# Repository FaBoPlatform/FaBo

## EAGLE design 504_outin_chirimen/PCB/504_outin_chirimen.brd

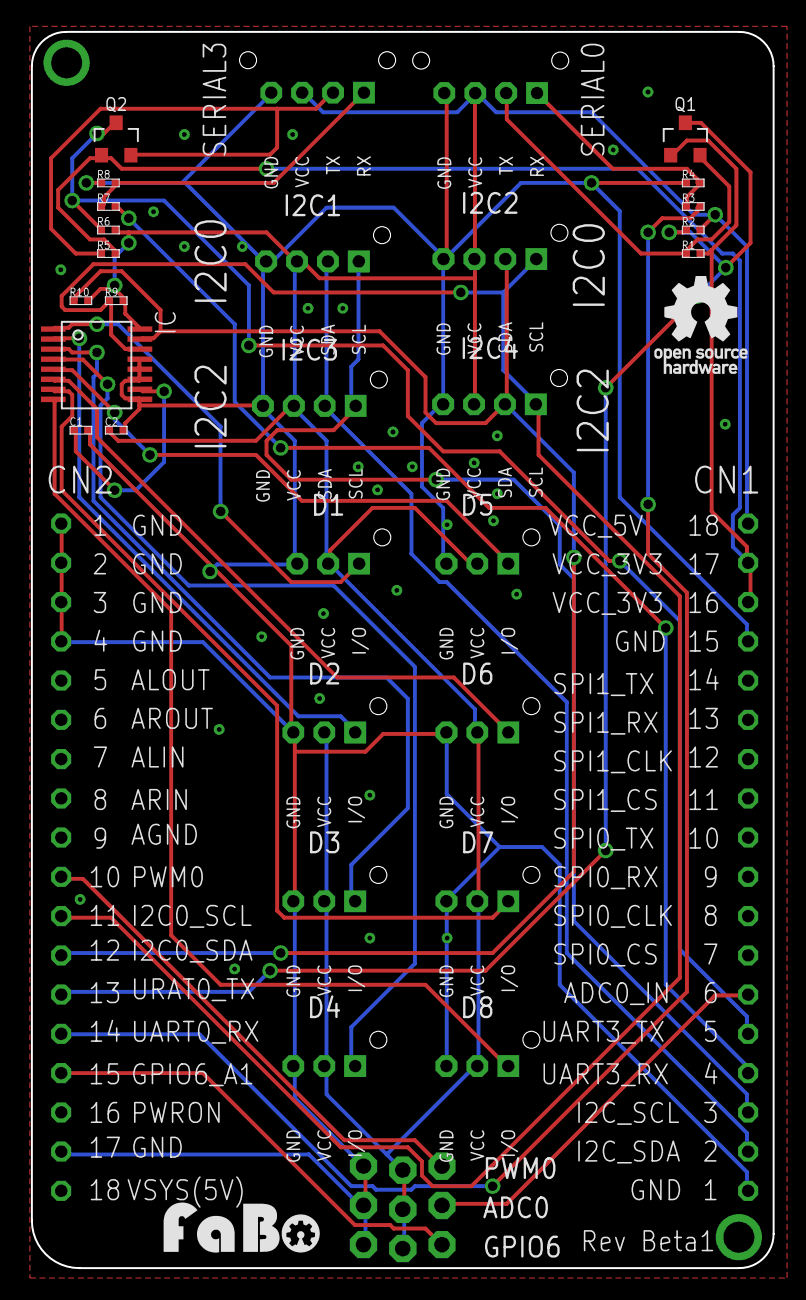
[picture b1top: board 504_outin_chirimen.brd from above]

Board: 2 copper layers, 48.0 x 80.0 mm, 35 parts (0 on the bottom side), 27 nets.

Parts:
ADC0: FABO_BRICK_3PIN_HEADER
C1: 0.1uf; 0402
C2: 1uf; 0402
D1, D2, D3, D4, D5, D6, D7, D8: FABO_BRICK_3PIN_B03B-PASK-1_SILK
GPIO6: FABO_BRICK_3PIN_HEADER
I2C1, I2C2, I2C3, I2C4: FABO_BRICK_I2C_B04B-PASK-1_SILK
IC: TI-ADS7828
J1, J2: FABO_BRICK_SERIAL_S04B-PASK-2_SILK
PWM0: FABO_BRICK_3PIN_HEADER
Q1, Q2: SOT23-3
R1, R2, R5, R6: 10k; 0402
R3, R7: 3k; 0402
R4, R8: 4.7k; 0402
R9, R10: 4.7K; 0402
U$2: FABO-CHIRIMEN
U$3: LOGO_OSHW_T_M
U$10: LOGO_FABO_MS

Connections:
3V3: Q1.1, Q2.1, R1.P$2, R5.P$2, U$2.CN1_16, U$2.CN1_17
5V: ADC0.VCC, C2.P$1, D1.VCC, D2.VCC, D3.VCC, D4.VCC, D5.VCC, D6.VCC, D7.VCC, D8.VCC, GPIO6.VCC, I2C1.VCC, I2C2.VCC, I2C3.VCC, I2C4.VCC, IC.16, J1.VCC, J2.VCC, PWM0.VCC, R2.P$2, R6.P$2, R9.P$2, R10.P$2, U$2.CN1_18
ADC0_IN: ADC0.I/O, U$2.CN1_6
CH0: D1.I/O, IC.1
CH1: D2.I/O, IC.2
CH2: D3.I/O, IC.3
CH3: D4.I/O, IC.4
CH4: D5.I/O, IC.5
CH5: D6.I/O, IC.6
CH6: D7.I/O, IC.7
CH7: D8.I/O, IC.8
GND: ADC0.GND, C1.P$2, C2.P$2, D1.GND, D2.GND, D3.GND, D4.GND, D5.GND, D6.GND, D7.GND, D8.GND, GPIO6.GND, I2C1.GND, I2C2.GND, I2C3.GND, I2C4.GND, IC.9, IC.11, IC.12, IC.13, J1.GND, J2.GND, PWM0.GND, R4.P$1, R8.P$1, U$2.CN1_1, U$2.CN1_15, U$2.CN2_1, U$2.CN2_2, U$2.CN2_3, U$2.CN2_4, U$2.CN2_17
GPIO6_A1: GPIO6.I/O, U$2.CN2_15
unnamed: C1.P$1, IC.10
PWM0: PWM0.I/O, U$2.CN2_10
RX0: J1.RX, R3.P$1, R4.P$2
RX3: J2.RX, R7.P$1, R8.P$2
SCL0: I2C2.SCL, I2C4.SCL, IC.14, R9.P$1, U$2.CN2_11
SCL2: I2C1.SCL, I2C3.SCL, U$2.CN1_3
SDA0: I2C2.SDA, I2C4.SDA, IC.15, R10.P$1, U$2.CN2_12
SDA2: I2C1.SDA, I2C3.SDA, U$2.CN1_2
TX0: J1.TX, Q1.2, R1.P$1
TX3: J2.TX, Q2.2, R5.P$1
UART0_RX: R3.P$2, U$2.CN2_14
UART0_TX: Q1.3, R2.P$1, U$2.CN2_13
UART3_RX: R7.P$2, U$2.CN1_4
UART3_TX: Q2.3, R6.P$1, U$2.CN1_5

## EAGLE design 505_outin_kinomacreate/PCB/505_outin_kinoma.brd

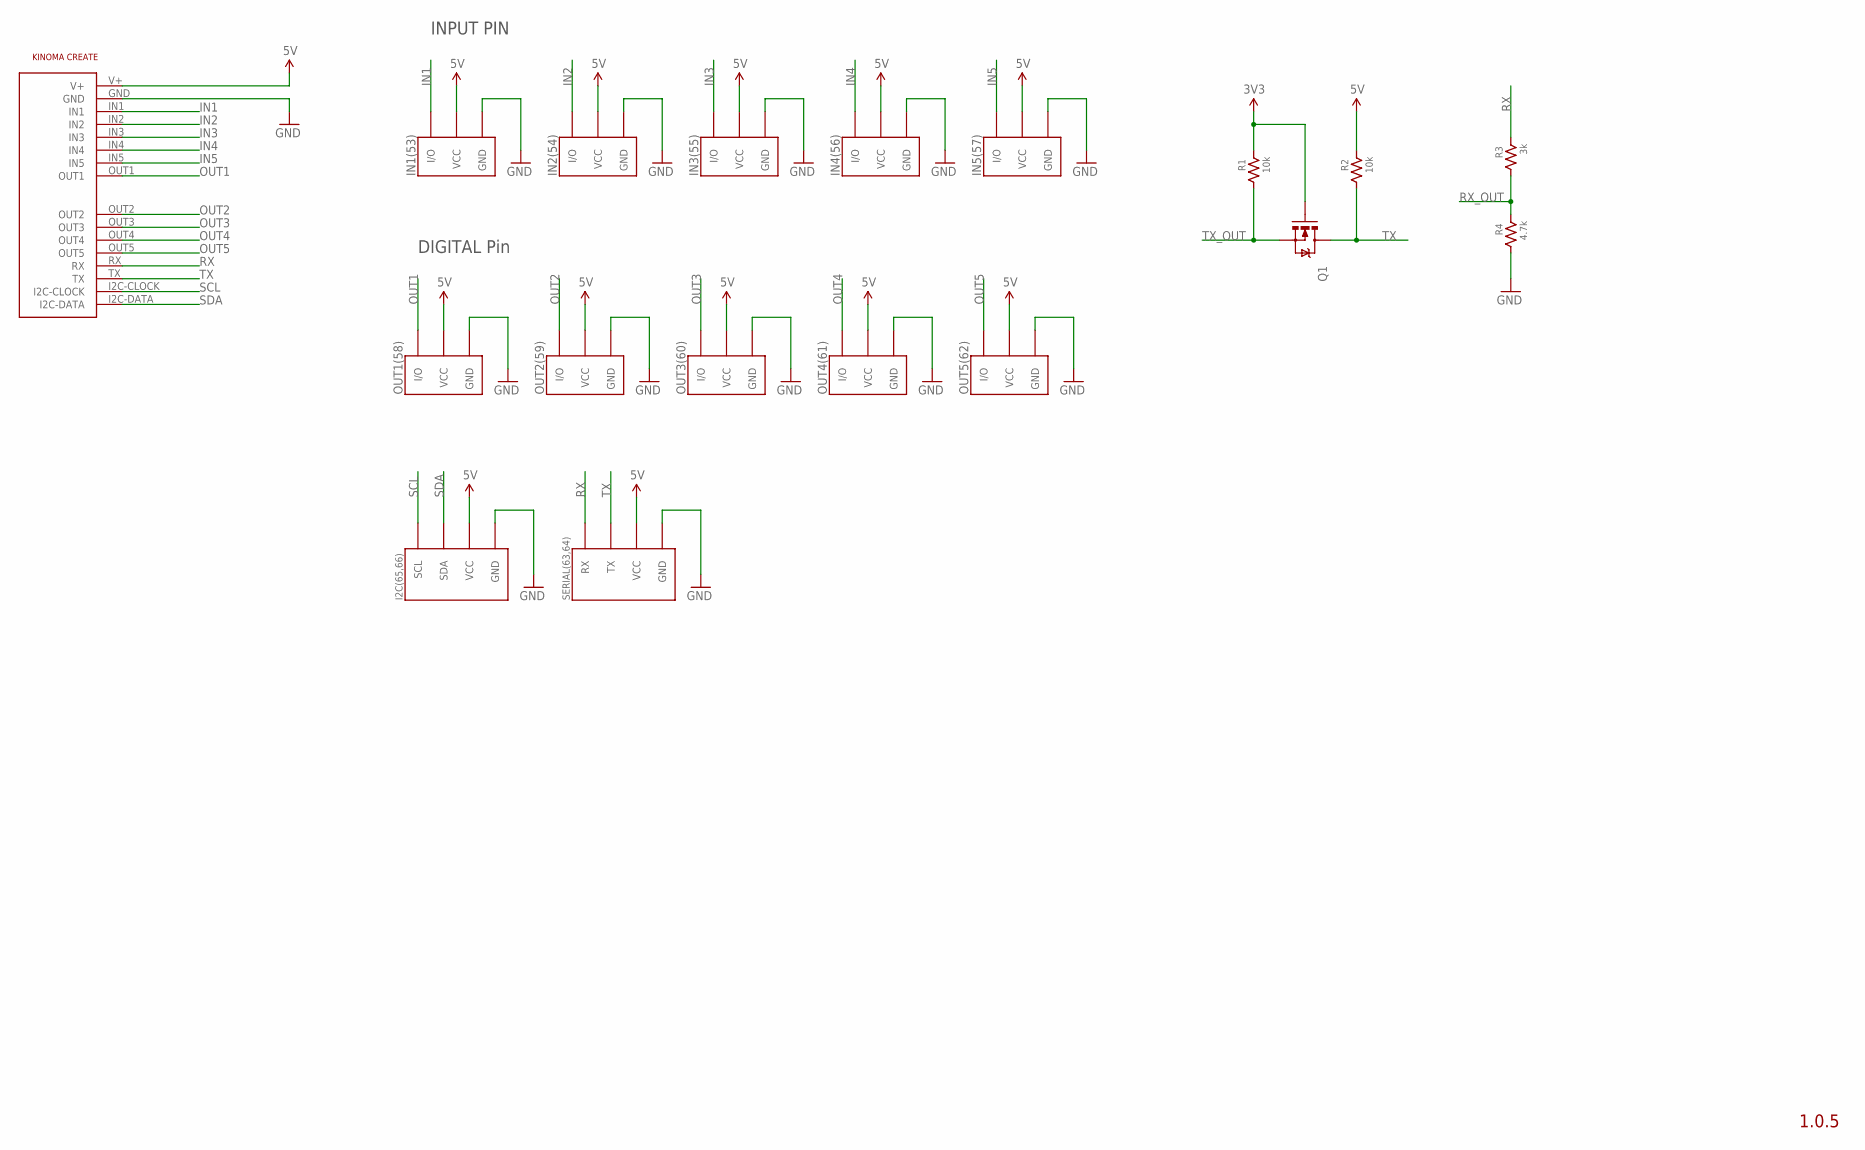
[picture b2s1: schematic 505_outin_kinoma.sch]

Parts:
I2C(65,66): I2C; FABO_BRICK_I2C_S04B-PASK-2
IN1(53), IN2(54), IN3(55), IN4(56), IN5(57): FABO_BRICK_3PIN-B03B-PASK-1; FABO_BRICK_3PIN_B03B-PASK-1
OUT1(58), OUT2(59), OUT3(60), OUT4(61), OUT5(62): FABO_BRICK_3PIN-B03B-PASK-1; FABO_BRICK_3PIN_B03B-PASK-1
Q1: MOSFET-N-BSS138; SOT23-3
R1, R2: 10k; 0402
R3: 3k; 0402
R4: 4.7k; 0402
SERIAL(63,64): FABO_BRICK_SERIAL-S04B-PASK-2; FABO_BRICK_SERIAL_S04B-PASK-2
U$18: FABO-KINOMA

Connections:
3V3: Q1.1 (G), R1.P$2 (2)
5V: I2C(65,66).VCC, IN1(53).VCC, IN2(54).VCC, IN3(55).VCC, IN4(56).VCC, IN5(57).VCC, OUT1(58).VCC, OUT2(59).VCC, OUT3(60).VCC, OUT4(61).VCC, OUT5(62).VCC, R2.P$2 (2), SERIAL(63,64).VCC, U$18.V+
GND: I2C(65,66).GND, IN1(53).GND, IN2(54).GND, IN3(55).GND, IN4(56).GND, IN5(57).GND, OUT1(58).GND, OUT2(59).GND, OUT3(60).GND, OUT4(61).GND, OUT5(62).GND, R4.P$1 (1), SERIAL(63,64).GND, U$18.GND
IN1: IN1(53).I/O, U$18.IN1
IN2: IN2(54).I/O, U$18.IN2
IN3: IN3(55).I/O, U$18.IN3
IN4: IN4(56).I/O, U$18.IN4
IN5: IN5(57).I/O, U$18.IN5
OUT1: OUT1(58).I/O, U$18.OUT1
OUT2: OUT2(59).I/O, U$18.OUT2
OUT3: OUT3(60).I/O, U$18.OUT3
OUT4: OUT4(61).I/O, U$18.OUT4
OUT5: OUT5(62).I/O, U$18.OUT5
RX: R3.P$2 (2), SERIAL(63,64).RX, U$18.RX
RX_OUT: R3.P$1 (1), R4.P$2 (2)
SCL: I2C(65,66).SCL, U$18.I2C-CLOCK
SDA: I2C(65,66).SDA, U$18.I2C-DATA
TX: Q1.3 (D), R2.P$1 (1), SERIAL(63,64).TX, U$18.TX
TX_OUT: Q1.2 (S), R1.P$1 (1)

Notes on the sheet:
1.0.5
DIGITAL Pin
INPUT PIN

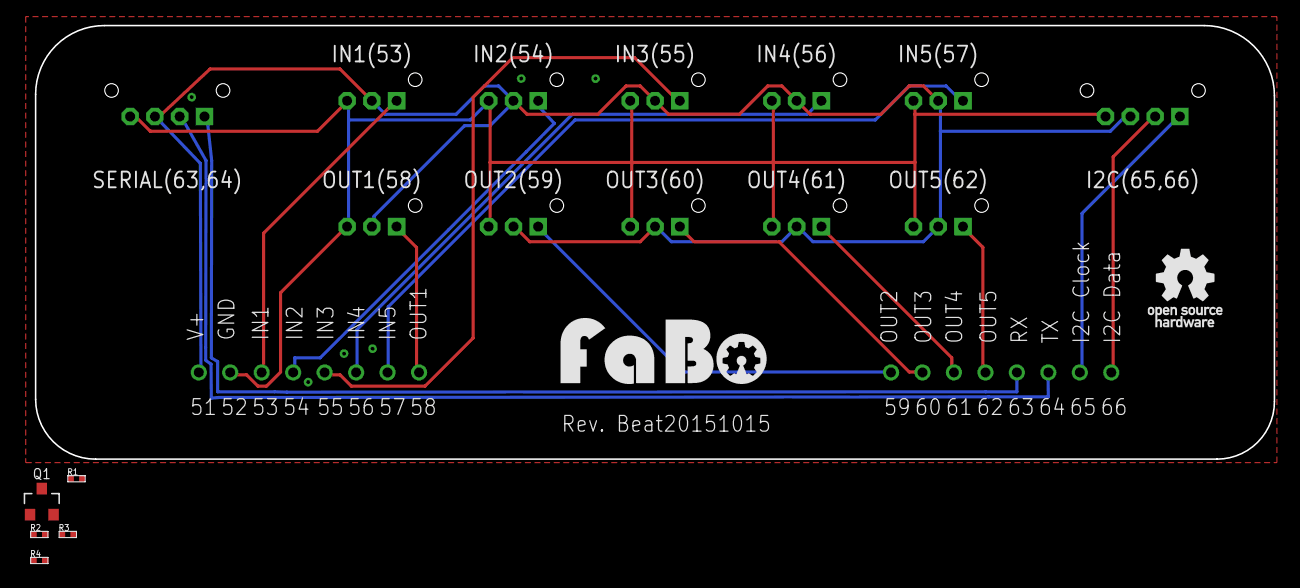
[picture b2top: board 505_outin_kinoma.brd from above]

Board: 2 copper layers, 100.0 x 35.0 mm, 20 parts (0 on the bottom side), 19 nets.

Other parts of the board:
U$2: LOGO_FABO_L
U$3: LOGO_OSHW_T_M

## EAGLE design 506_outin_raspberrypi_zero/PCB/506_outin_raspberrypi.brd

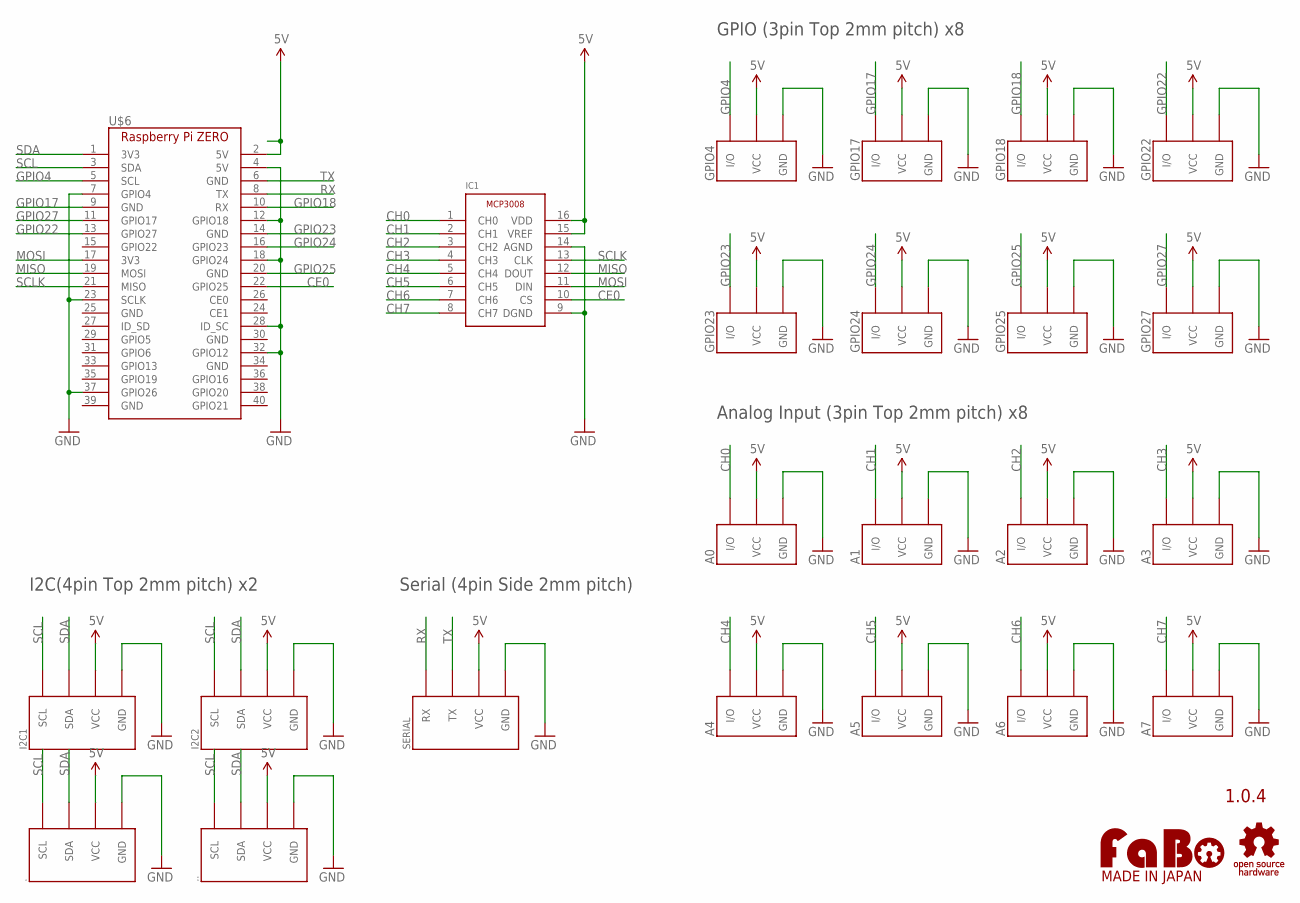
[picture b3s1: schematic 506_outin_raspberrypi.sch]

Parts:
., ..: FABO_BRICK_I2C-B04B-PASK-1; FABO_BRICK_I2C_B04B-PASK-1
A0, A1, A2, A3, A4, A5, A6, A7: FABO_BRICK_3PIN-B03B-PASK-1; FABO_BRICK_3PIN_B03B-PASK-1
GPIO4, GPIO17, GPIO18, GPIO22, GPIO23, GPIO24, GPIO25, GPIO27: FABO_BRICK_3PIN-B03B-PASK-1; FABO_BRICK_3PIN_B03B-PASK-1
I2C1, I2C2: FABO_BRICK_I2C-B04B-PASK-1; FABO_BRICK_I2C_B04B-PASK-1
IC1: MICROCHIP-MCP3008
SERIAL: FABO_BRICK_SERIAL-S04B-PASK-2; FABO_BRICK_SERIAL_S04B-PASK-2
U$4: LOGO_OSHW-T_M; LOGO_OSHW_T_MS
U$6: RASPBERRY_PI_ZERO
U$14: LOGO_FABO-M; LOGO_FABO_MS

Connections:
5V: ..VCC, ...VCC, A0.VCC, A1.VCC, A2.VCC, A3.VCC, A4.VCC, A5.VCC, A6.VCC, A7.VCC, GPIO4.VCC, GPIO17.VCC, GPIO18.VCC, GPIO22.VCC, GPIO23.VCC, GPIO24.VCC, GPIO25.VCC, GPIO27.VCC, I2C1.VCC, I2C2.VCC, IC1.15 (VREF), IC1.16 (VDD), SERIAL.VCC, U$6.2 (5V)
CE0: IC1.10 (CS), U$6.22 (GPIO25)
CH0: A0.I/O, IC1.1 (CH0)
CH1: A1.I/O, IC1.2 (CH1)
CH2: A2.I/O, IC1.3 (CH2)
CH3: A3.I/O, IC1.4 (CH3)
CH4: A4.I/O, IC1.5 (CH4)
CH5: A5.I/O, IC1.6 (CH5)
CH6: A6.I/O, IC1.7 (CH6)
CH7: A7.I/O, IC1.8 (CH7)
GND: ..GND, ...GND, A0.GND, A1.GND, A2.GND, A3.GND, A4.GND, A5.GND, A6.GND, A7.GND, GPIO4.GND, GPIO17.GND, GPIO18.GND, GPIO22.GND, GPIO23.GND, GPIO24.GND, GPIO25.GND, GPIO27.GND, I2C1.GND, I2C2.GND, IC1.9 (DGND), IC1.14 (AGND), SERIAL.GND, U$6.4 (5V), U$6.7 (GPIO4), U$6.12 (GPIO18), U$6.18 (GPIO24), U$6.23 (SCLK), U$6.28 (ID_SC), U$6.32 (GPIO12), U$6.37 (GPIO26)
GPIO4: GPIO4.I/O, U$6.5 (SCL)
GPIO17: GPIO17.I/O, U$6.9 (GND)
GPIO18: GPIO18.I/O, U$6.10 (RX)
GPIO22: GPIO22.I/O, U$6.13 (GPIO27)
GPIO23: GPIO23.I/O, U$6.14 (GND)
GPIO24: GPIO24.I/O, U$6.16 (GPIO23)
GPIO25: GPIO25.I/O, U$6.20 (GND)
GPIO27: GPIO27.I/O, U$6.11 (GPIO17)
MISO: IC1.12 (DOUT), U$6.19 (MOSI)
MOSI: IC1.11 (DIN), U$6.17 (3V3)
RX: SERIAL.RX, U$6.8 (TX)
SCL: ..SCL, ...SCL, I2C1.SCL, I2C2.SCL, U$6.3 (SDA)
SCLK: IC1.13 (CLK), U$6.21 (MISO)
SDA: ..SDA, ...SDA, I2C1.SDA, I2C2.SDA, U$6.1 (3V3)
TX: SERIAL.TX, U$6.6 (GND)

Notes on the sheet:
1.0.4
GPIO (3pin Top 2mm pitch) x8
I2C(4pin Top 2mm pitch) x2
Analog Input (3pin Top 2mm pitch) x8
Serial (4pin Side 2mm pitch)

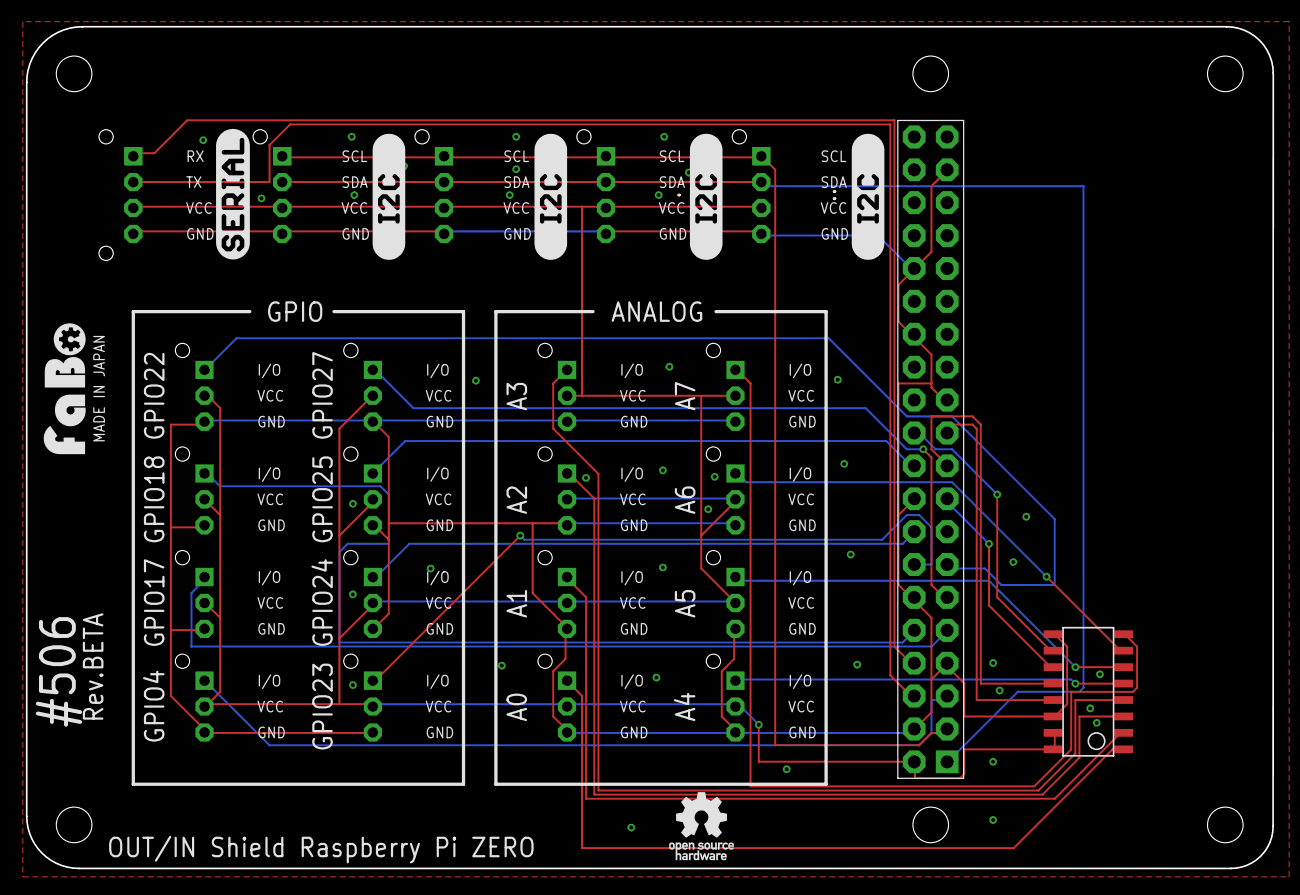
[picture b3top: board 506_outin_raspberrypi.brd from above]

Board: 2 copper layers, 96.3 x 65.0 mm, 30 parts (0 on the bottom side), 26 nets.

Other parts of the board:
U$2, U$5, U$7, U$8: LOGO_SILK_I2C
U$3: LOGO_SILK_SERIAL2

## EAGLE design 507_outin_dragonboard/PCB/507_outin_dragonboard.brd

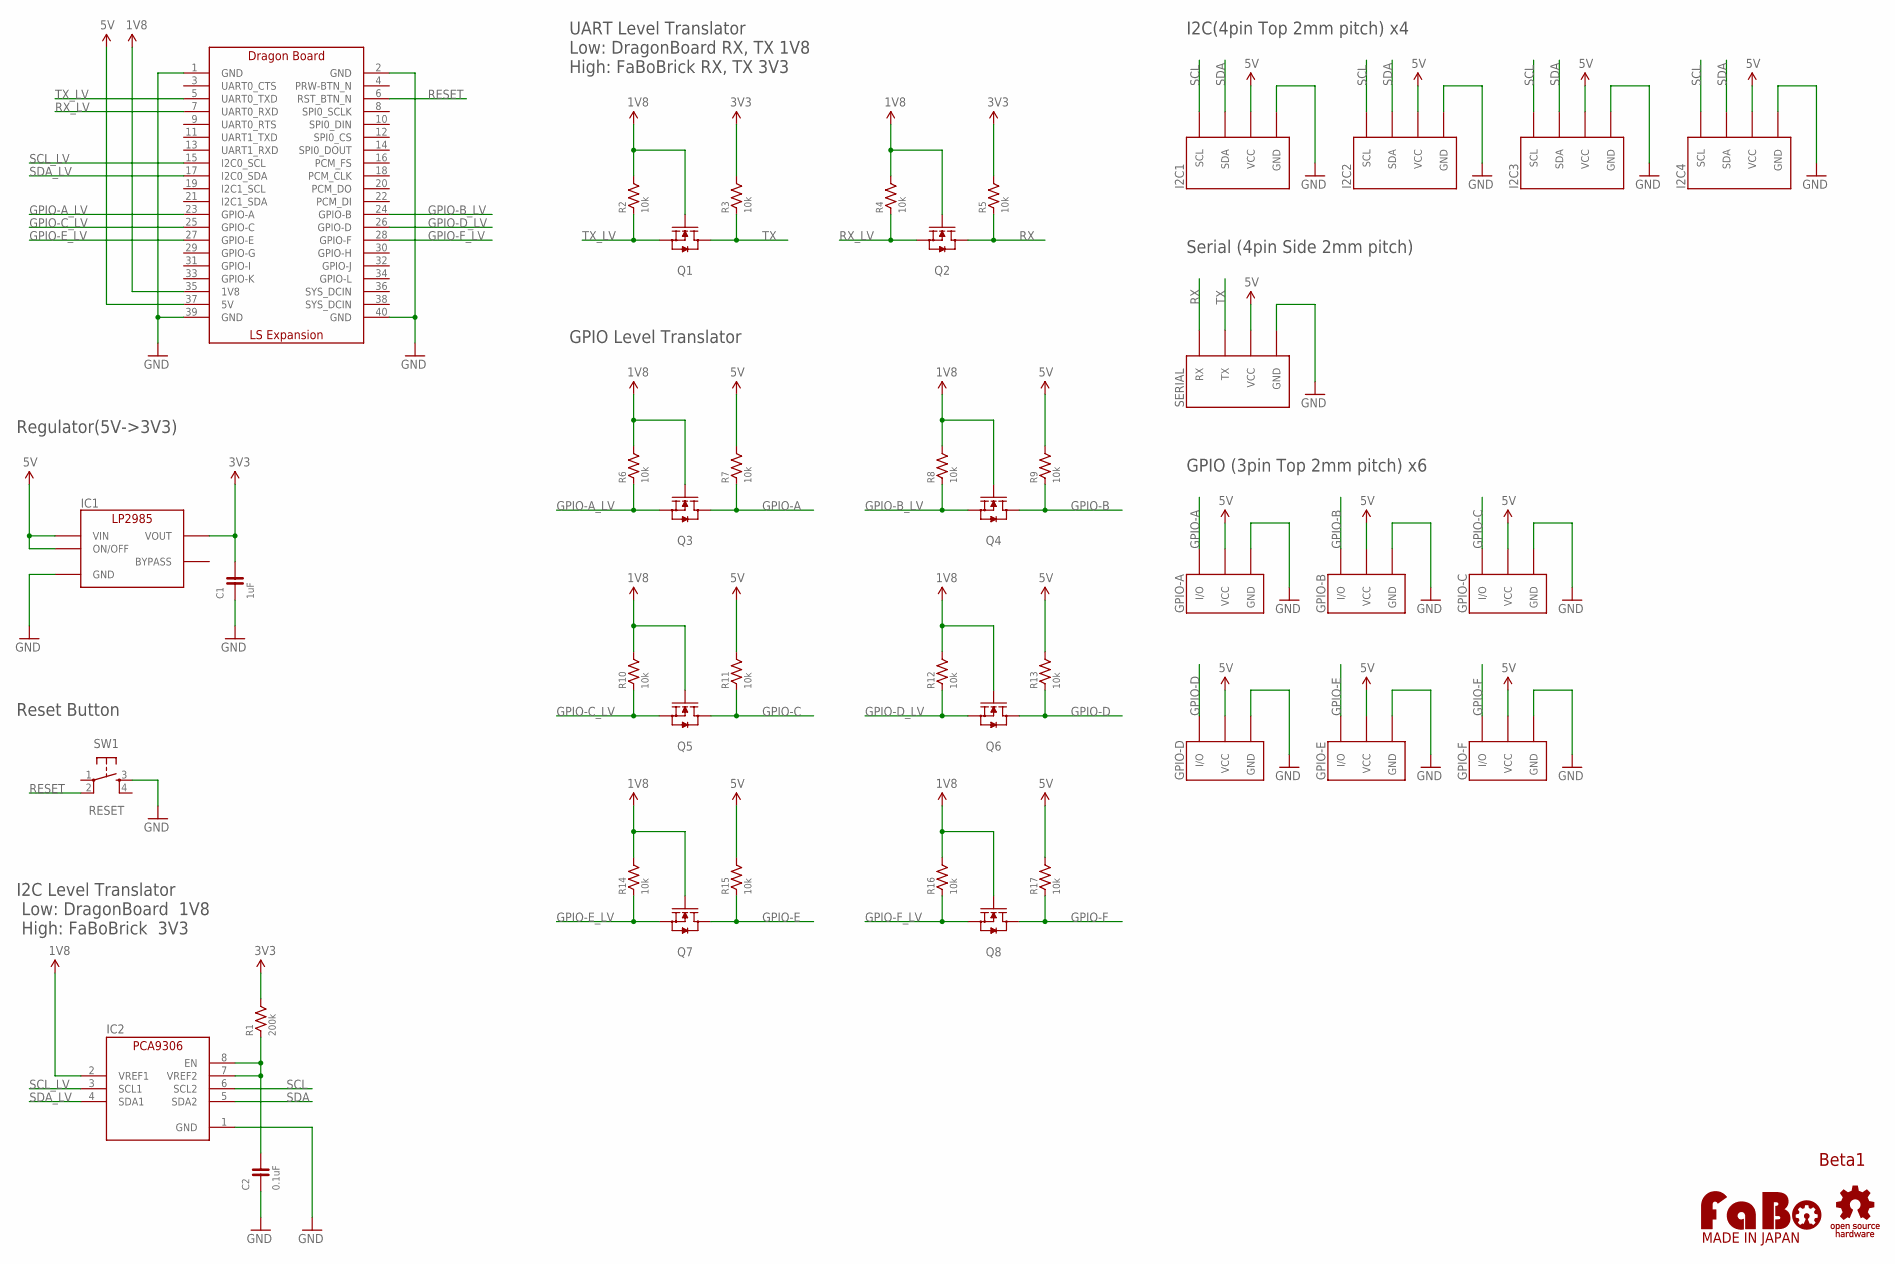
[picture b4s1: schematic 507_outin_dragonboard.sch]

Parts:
C1: 1uF; 0603
C2: 0.1uF; 0603
GPIO-A: FABO_BRICK_3PIN-B03B-PASK-1; FABO_BRICK_3PIN_B03B-PASK-1
GPIO-B: FABO_BRICK_3PIN-B03B-PASK-1; FABO_BRICK_3PIN_B03B-PASK-1
GPIO-C: FABO_BRICK_3PIN-B03B-PASK-1; FABO_BRICK_3PIN_B03B-PASK-1
GPIO-D: FABO_BRICK_3PIN-B03B-PASK-1; FABO_BRICK_3PIN_B03B-PASK-1
GPIO-E: FABO_BRICK_3PIN-B03B-PASK-1; FABO_BRICK_3PIN_B03B-PASK-1
GPIO-F: FABO_BRICK_3PIN-B03B-PASK-1; FABO_BRICK_3PIN_B03B-PASK-1
I2C1, I2C2, I2C3, I2C4: FABO_BRICK_I2C-B04B-PASK-1; FABO_BRICK_I2C_B04B-PASK-1
IC1: TI-LP2985-33DBVR; TI-LP2985
IC2: TI-PCA9306DQE; TI-PCA9306
Q1, Q2, Q3, Q4, Q5, Q6, Q7, Q8: MOSFET-N-BSS138; SOT23-3
R1: 200k; 0603
R2, R3, R4, R5, R6, R7, R8, R9, R10, R11, R12, R13, R14, R15, R16, R17: 10k; 0603
SERIAL: FABO_BRICK_SERIAL-S04B-PASK-2; FABO_BRICK_SERIAL_S04B-PASK-2
SW1: RESET; DTS_6_V
U1: FABO-DRAGONBOARD
U$4: LOGO_OSHW-T_M_BOTTOM; LOGO_OSHW_T_MS_BOTTOM
U$8: LOGO_FABO-M; LOGO_FABO_MS

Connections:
1V8: IC2.2 (VREF1), Q1.1 (G), Q2.1 (G), Q3.1 (G), Q4.1 (G), Q5.1 (G), Q6.1 (G), Q7.1 (G), Q8.1 (G), R2.2, R4.2, R6.2, R8.2, R10.2, R12.2, R14.2, R16.2, U1.35 (1V8)
3V3: C1.2, IC1.5 (VOUT), R1.2, R3.2, R5.2
5V: GPIO-A.VCC, GPIO-B.VCC, GPIO-C.VCC, GPIO-D.VCC, GPIO-E.VCC, GPIO-F.VCC, I2C1.VCC, I2C2.VCC, I2C3.VCC, I2C4.VCC, IC1.1 (VIN), IC1.3 (ON/OFF), R7.2, R9.2, R11.2, R13.2, R15.2, R17.2, SERIAL.VCC, U1.37 (5V)
GND: C1.1, C2.1, GPIO-A.GND, GPIO-B.GND, GPIO-C.GND, GPIO-D.GND, GPIO-E.GND, GPIO-F.GND, I2C1.GND, I2C2.GND, I2C3.GND, I2C4.GND, IC1.2 (GND), IC2.1 (GND), SERIAL.GND, SW1.3, U1.1 (GND), U1.2 (GND), U1.39 (GND), U1.40 (GND)
GPIO-A: GPIO-A.I/O, Q3.3 (D), R7.1
GPIO-A_LV: Q3.2 (S), R6.1, U1.23 (GPIO-A)
GPIO-B: GPIO-B.I/O, Q4.3 (D), R9.1
GPIO-B_LV: Q4.2 (S), R8.1, U1.24 (GPIO-B)
GPIO-C: GPIO-C.I/O, Q5.3 (D), R11.1
GPIO-C_LV: Q5.2 (S), R10.1, U1.25 (GPIO-C)
GPIO-D: GPIO-D.I/O, Q6.3 (D), R13.1
GPIO-D_LV: Q6.2 (S), R12.1, U1.26 (GPIO-D)
GPIO-E: GPIO-E.I/O, Q7.3 (D), R15.1
GPIO-E_LV: Q7.2 (S), R14.1, U1.27 (GPIO-E)
GPIO-F: GPIO-F.I/O, Q8.3 (D), R17.1
GPIO-F_LV: Q8.2 (S), R16.1, U1.28 (GPIO-F)
unnamed: C2.2, IC2.7 (VREF2), IC2.8 (EN), R1.1
RESET: SW1.2, U1.6 (RST_BTN_N)
RX: Q2.3 (D), R5.1, SERIAL.RX
RX_LV: Q2.2 (S), R4.1, U1.7 (UART0_RXD)
SCL: I2C1.SCL, I2C2.SCL, I2C3.SCL, I2C4.SCL, IC2.6 (SCL2)
SCL_LV: IC2.3 (SCL1), U1.15 (I2C0_SCL)
SDA: I2C1.SDA, I2C2.SDA, I2C3.SDA, I2C4.SDA, IC2.5 (SDA2)
SDA_LV: IC2.4 (SDA1), U1.17 (I2C0_SDA)
TX: Q1.3 (D), R3.1, SERIAL.TX
TX_LV: Q1.2 (S), R2.1, U1.5 (UART0_TXD)

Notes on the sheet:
Beta1
UART Level Translator Low: DragonBoard RX, TX 1V8 High: FaBoBrick RX, TX 3V3
I2C(4pin Top 2mm pitch) x4
Serial (4pin Side 2mm pitch)
I2C Level Translator Low: DragonBoard 1V8 High: FaBoBrick 3V3
Regulator(5V->3V3)
Reset Button
GPIO (3pin Top 2mm pitch) x6
GPIO Level Translator

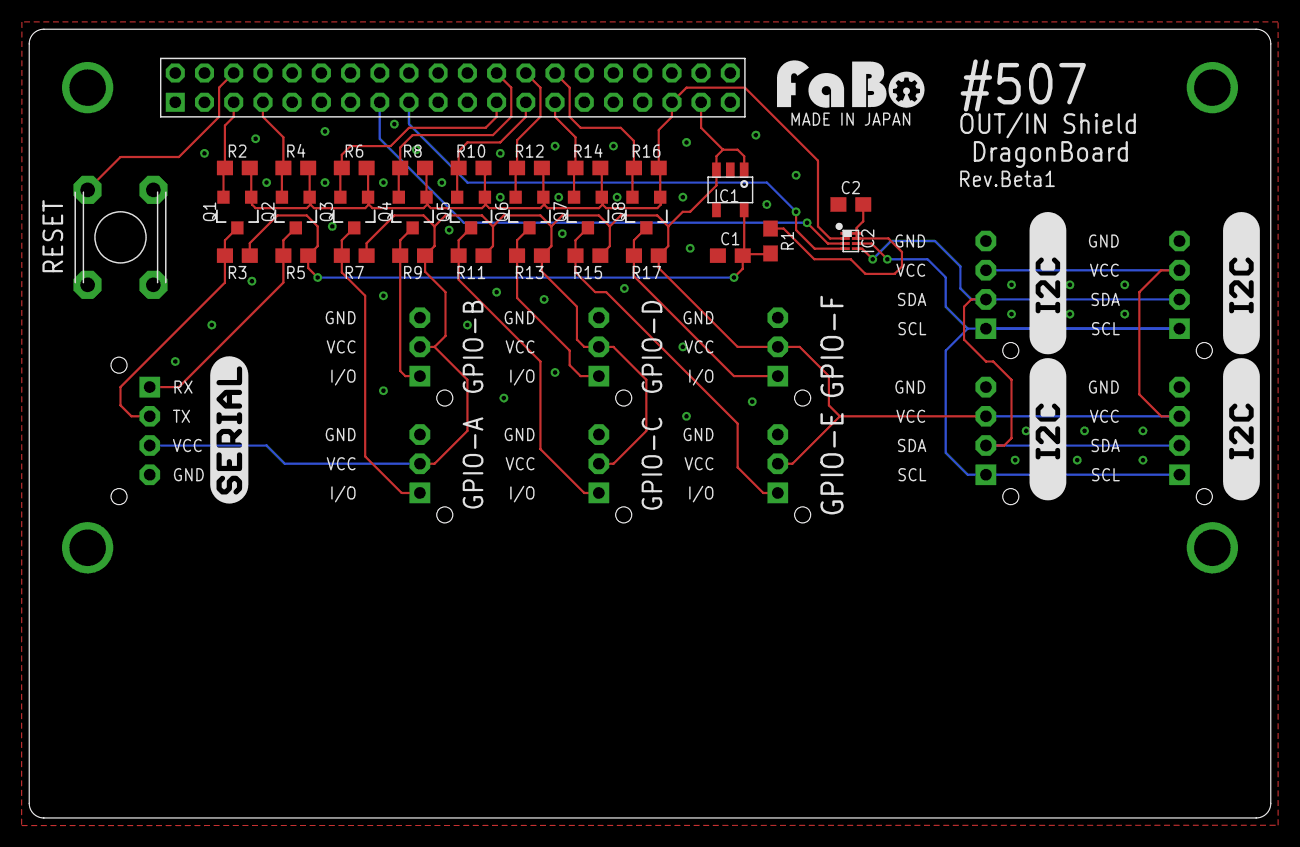
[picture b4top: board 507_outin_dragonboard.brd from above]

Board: 2 copper layers, 85.0 x 54.0 mm, 49 parts (0 on the bottom side), 26 nets.

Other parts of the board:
U$2, U$5, U$6, U$7: LOGO_SILK_I2C
U$3: LOGO_SILK_SERIAL2

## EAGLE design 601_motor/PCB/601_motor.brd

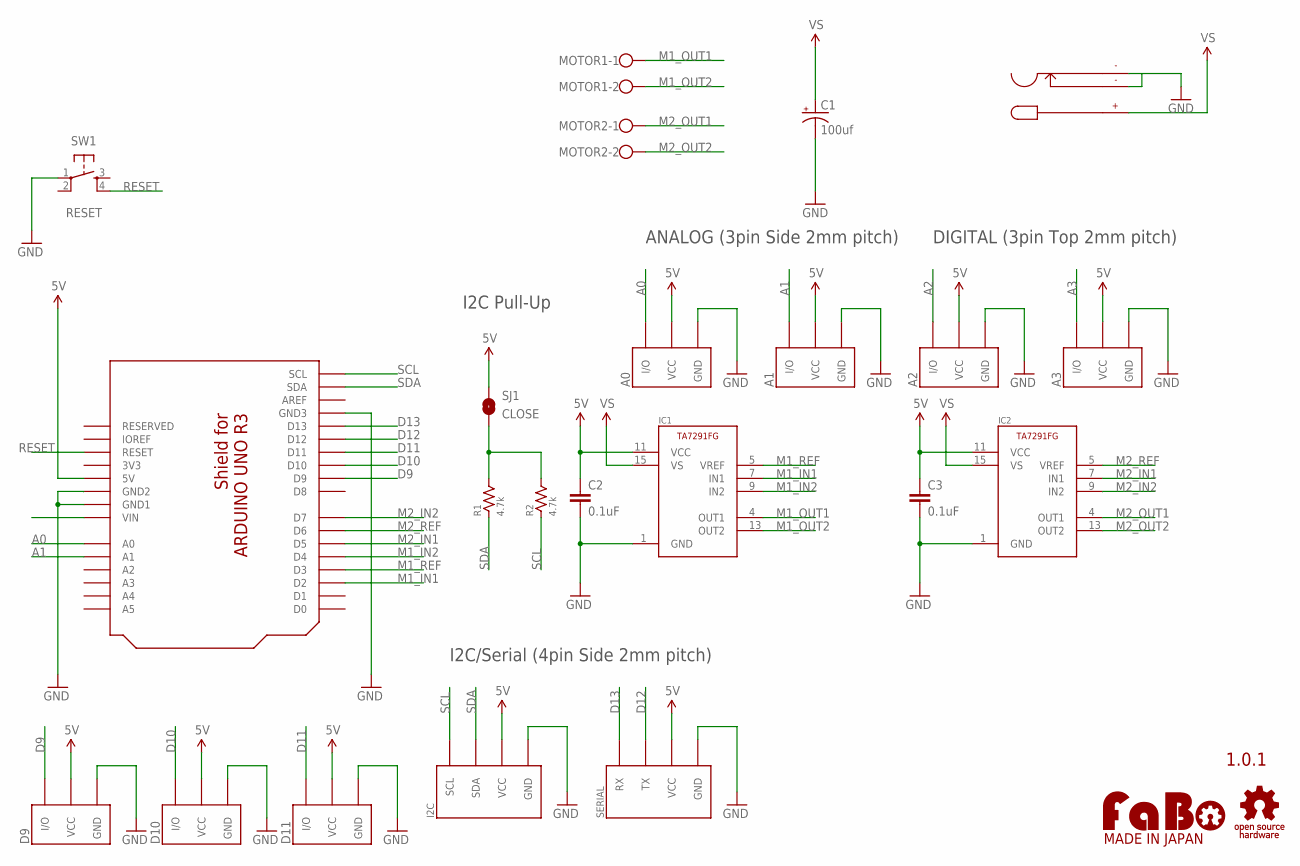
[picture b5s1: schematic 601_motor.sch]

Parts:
A0, A1, A2, A3: FABO_BRICK_3PIN-S03B-PASK-2; FABO_BRICK_3PIN_S03B-PASK-2
C1: 100uf; 153CLV-0405
C2, C3: 0.1uF; EIA0603
D9, D10, D11: FABO_BRICK_3PIN-HEADER; FABO_BRICK_3PIN_HEADER
I2C: FABO_BRICK_I2C-S04B-PASK-2; FABO_BRICK_I2C_S04B-PASK-2
IC1, IC2: MOTOR-DRIVER-TA7291FG
MOTOR1, MOTOR2: W237-102
R1, R2: 4.7k; 0603
SERIAL: FABO_BRICK_SERIAL-S04B-PASK-2; FABO_BRICK_SERIAL_S04B-PASK-2
SJ1: CLOSE; SMD-JUMPER-2-CLOSE
SW1: RESET; DTS_6_V
U1: ARDUINO_UNO_R3_SHIELD-NOLABEL; ARDUINO_UNO_R3_NOLABEL
U$2: DCJACK-MJ179PH; MJ179PH
U$6: LOGO_OSHW-T_M; LOGO_OSHW_T_MS
U$7: LOGO_FABO-M; LOGO_FABO_MS

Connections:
3V3: U1.3V3
5V: A0.VCC, A1.VCC, A2.VCC, A3.VCC, C2.1, C3.1, D9.VCC, D10.VCC, D11.VCC, I2C.VCC, IC1.11 (VCC), IC2.11 (VCC), SERIAL.VCC, SJ1.1, U1.5V
A0: A0.I/O, U1.A0
A1: A1.I/O, U1.A1
A2: A2.I/O
A3: A3.I/O
D9: D9.I/O, U1.D9
D10: D10.I/O, U1.D10
D11: D11.I/O, U1.D11
D12: SERIAL.TX, U1.D12
D13: SERIAL.RX, U1.D13
GND: A0.GND, A1.GND, A2.GND, A3.GND, C1.-, C2.2, C3.2, D9.GND, D10.GND, D11.GND, I2C.GND, IC1.1 (GND), IC2.1 (GND), SERIAL.GND, SW1.1, U1.GND1, U1.GND2, U1.GND3, U$2.-@1 (-), U$2.-@2 (-)
M1_IN1: IC1.7 (IN1), U1.D2
M1_IN2: IC1.9 (IN2), U1.D4
M1_OUT1: IC1.4 (OUT1), MOTOR1.1
M1_OUT2: IC1.13 (OUT2), MOTOR1.2
M1_REF: IC1.5 (VREF), U1.D3
M2_IN1: IC2.7 (IN1), U1.D5
M2_IN2: IC2.9 (IN2), U1.D7
M2_OUT1: IC2.4 (OUT1), MOTOR2.1
M2_OUT2: IC2.13 (OUT2), MOTOR2.2
M2_REF: IC2.5 (VREF), U1.D6
unnamed: R1.2, R2.2, SJ1.2
RESET: SW1.4, U1.RESET
SCL: I2C.SCL, R2.1, U1.SCL
SDA: I2C.SDA, R1.1, U1.SDA
VCC: U1.VIN
VS: C1.+, IC1.15 (VS), IC2.15 (VS), U$2.+

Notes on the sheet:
1.0.1
I2C/Serial (4pin Side 2mm pitch)
DIGITAL (3pin Top 2mm pitch)
ANALOG (3pin Side 2mm pitch)
I2C Pull-Up

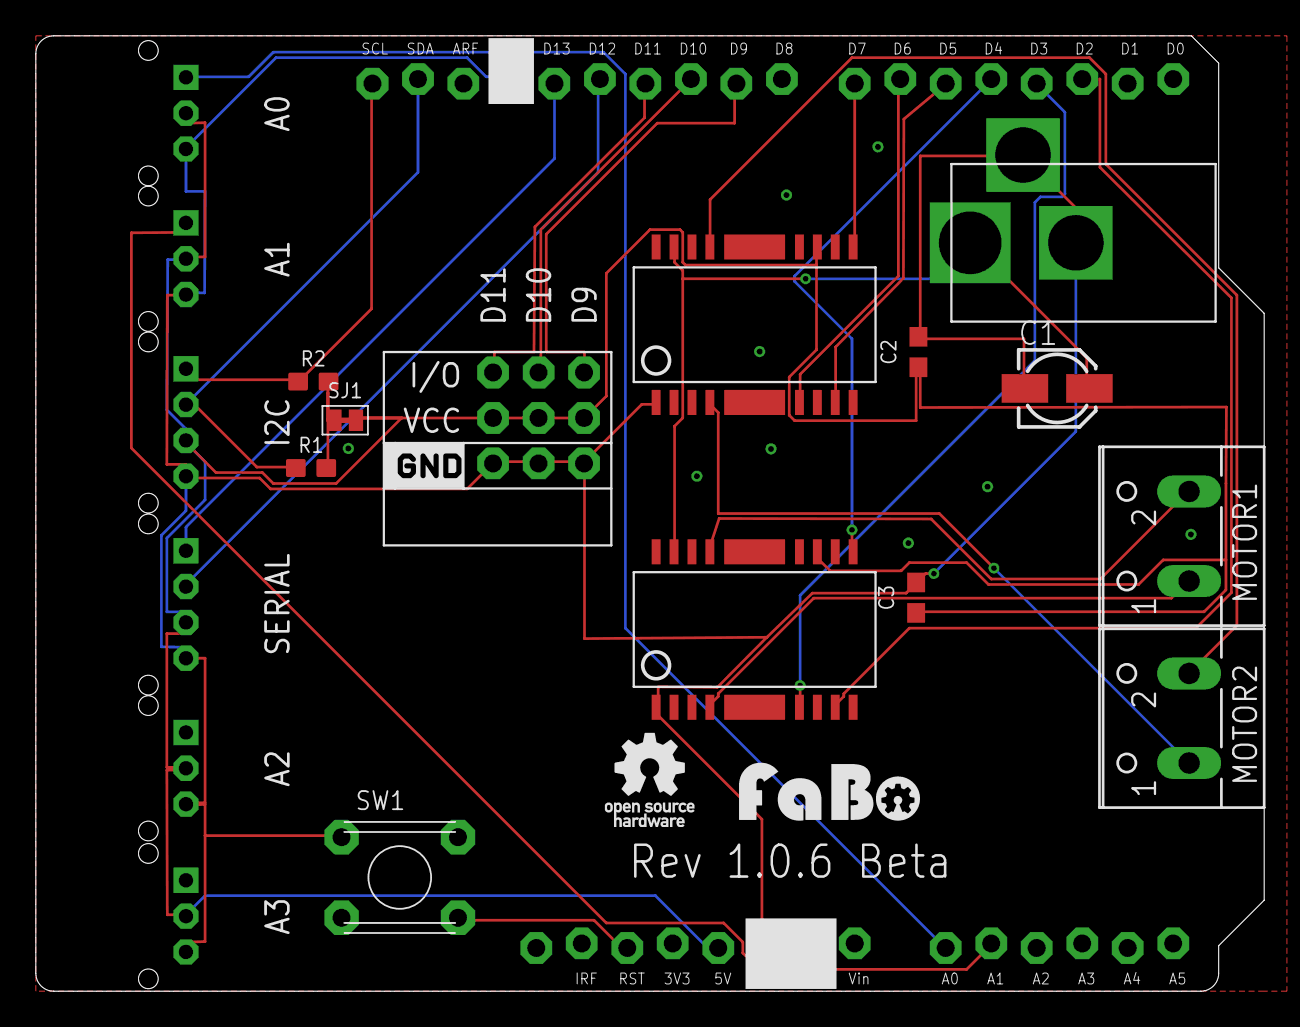
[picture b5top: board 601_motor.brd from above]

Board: 2 copper layers, 68.6 x 53.3 mm, 25 parts (0 on the bottom side), 24 nets.

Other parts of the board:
U$19: LOGO_SILK_GND

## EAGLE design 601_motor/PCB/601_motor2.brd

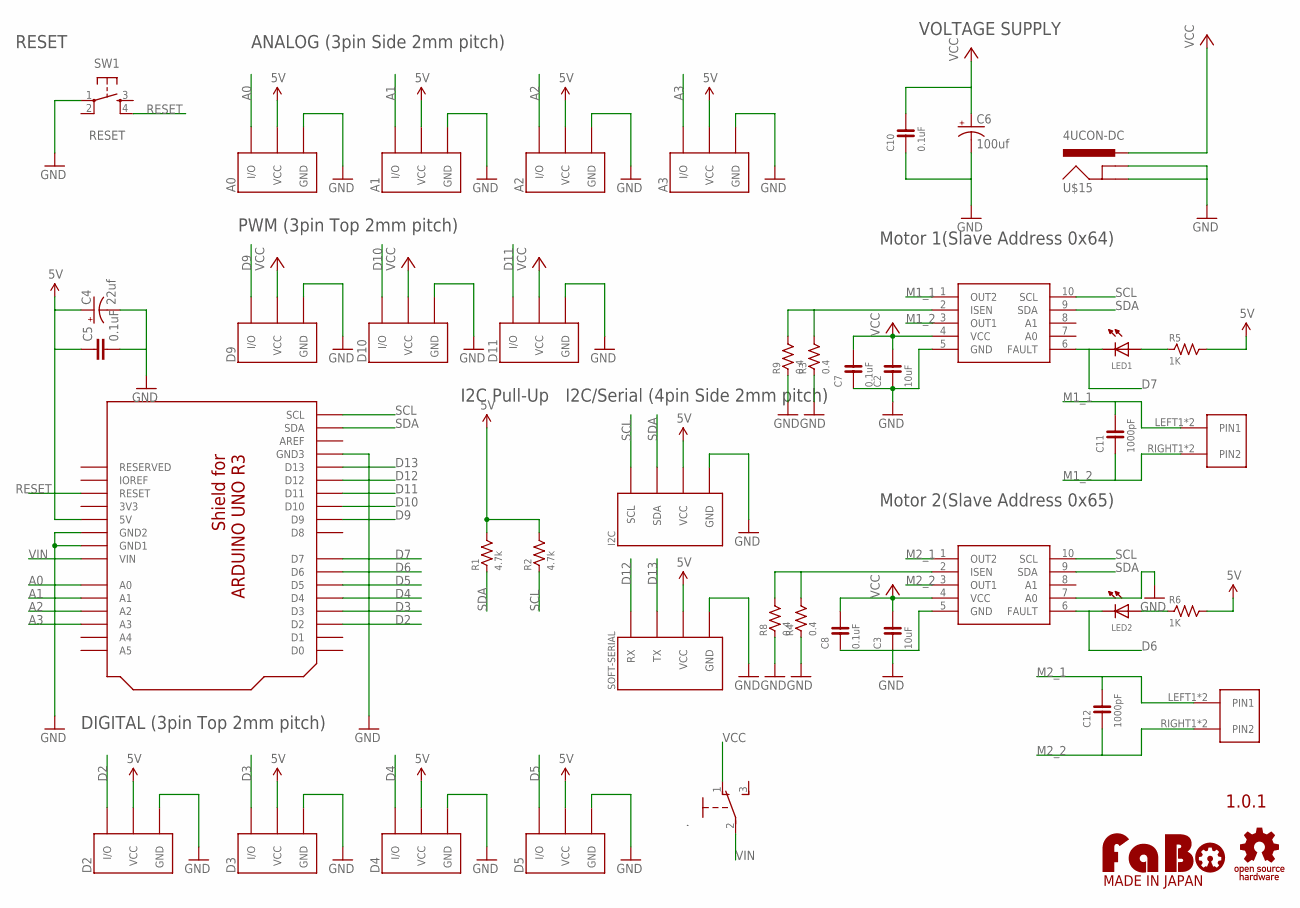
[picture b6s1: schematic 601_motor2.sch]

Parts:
.: SLIDE-EG1218; EG1218
A0, A1, A2, A3: FABO_BRICK_3PIN-S03B-PASK-2; FABO_BRICK_3PIN_S03B-PASK-2
C2, C3: 10uF; 0603
C4: 22uf; 153CLV-0405
C5: 0.1uF; EIA0603
C6: 100uf; 153CLV-0405
C7, C8, C10: 0.1uF; 0603
C11, C12: 1000pF; 0603
D2, D3, D4, D5: FABO_BRICK_3PIN-B03B-PASK-1; FABO_BRICK_3PIN_B03B-PASK-1
D9, D10, D11: FABO_BRICK_3PIN-HEADER; FABO_BRICK_3PIN_HEADER
I2C: FABO_BRICK_I2C-S04B-PASK-2; FABO_BRICK_I2C_S04B-PASK-2
LED1, LED2: LED-0603; 0603
R1, R2: 4.7k; 0603
R3, R4, R8, R9: 0.4; 0603
R5, R6: 1K; 0603
SOFT-SERIAL: FABO_BRICK_SERIAL-S04B-PASK-2; FABO_BRICK_SERIAL_S04B-PASK-2
SW1: RESET; DTS_6_V
U1: ARDUINO_UNO_R3_SHIELD-NOLABEL; ARDUINO_UNO_R3_NOLABEL
U$6: LOGO_OSHW-T_M; LOGO_OSHW_T_MS
U$7: LOGO_FABO-M; LOGO_FABO_MS
U$8, U$10: DRV8830
U$12, U$13: ML-1400-S1
U$15: 4UCON-DC

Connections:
3V3: U1.3V3
5V: A0.VCC, A1.VCC, A2.VCC, A3.VCC, C4.+, C5.1, D2.VCC, D3.VCC, D4.VCC, D5.VCC, I2C.VCC, R1.2, R2.2, R5.2, R6.2, SOFT-SERIAL.VCC, U1.5V
A0: A0.I/O, U1.A0
A1: A1.I/O, U1.A1
A2: A2.I/O, U1.A2
A3: A3.I/O, U1.A3
D2: D2.I/O, U1.D2
D3: D3.I/O, U1.D3
D4: D4.I/O, U1.D4
D5: D5.I/O, U1.D5
D6: LED2.CATHODE, U1.D6, U$10.6 (FAULT)
D7: LED1.CATHODE, U1.D7, U$8.6 (FAULT)
D9: D9.I/O, U1.D9
D10: D10.I/O, U1.D10
D11: D11.I/O, U1.D11
D12: SOFT-SERIAL.RX, U1.D12
D13: SOFT-SERIAL.TX, U1.D13
GND: A0.GND, A1.GND, A2.GND, A3.GND, C2.1, C3.1, C4.-, C5.2, C6.-, C7.1, C8.1, C10.1, D2.GND, D3.GND, D4.GND, D5.GND, D9.GND, D10.GND, D11.GND, I2C.GND, R3.1, R4.1, R8.1, R9.1, SOFT-SERIAL.GND, SW1.1, U1.GND1, U1.GND2, U1.GND3, U$8.5 (GND), U$10.5 (GND), U$10.7 (A0), U$15.GND1 (GND), U$15.GND2 (GNDBREAK)
M1_1: C11.2, U$8.1 (OUT2), U$12.LEFT1 (PIN1), U$12.LEFT2 (PIN1)
M1_2: C11.1, U$8.3 (OUT1), U$12.RIGHT1 (PIN2), U$12.RIGHT2 (PIN2)
M2_1: C12.2, U$10.1 (OUT2), U$13.LEFT1 (PIN1), U$13.LEFT2 (PIN1)
M2_2: C12.1, U$10.3 (OUT1), U$13.RIGHT1 (PIN2), U$13.RIGHT2 (PIN2)
unnamed: R3.2, R9.2, U$8.2 (ISEN)
unnamed: R4.2, R8.2, U$10.2 (ISEN)
unnamed: LED1.ANODE, R5.1
unnamed: LED2.ANODE, R6.1
RESET: SW1.4, U1.RESET
SCL: I2C.SCL, R2.1, U1.SCL, U$8.10 (SCL), U$10.10 (SCL)
SDA: I2C.SDA, R1.1, U1.SDA, U$8.9 (SDA), U$10.9 (SDA)
VCC: ..1, C2.2, C3.2, C6.+, C7.2, C8.2, C10.2, D9.VCC, D10.VCC, D11.VCC, U$8.4 (VCC), U$10.4 (VCC), U$15.VCC (PWR)
VIN: ..2, U1.VIN

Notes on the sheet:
1.0.1
I2C/Serial (4pin Side 2mm pitch)
PWM (3pin Top 2mm pitch)
ANALOG (3pin Side 2mm pitch)
I2C Pull-Up
VOLTAGE SUPPLY
DIGITAL (3pin Top 2mm pitch)
RESET
Motor 1(Slave Address 0x64)
Motor 2(Slave Address 0x65)

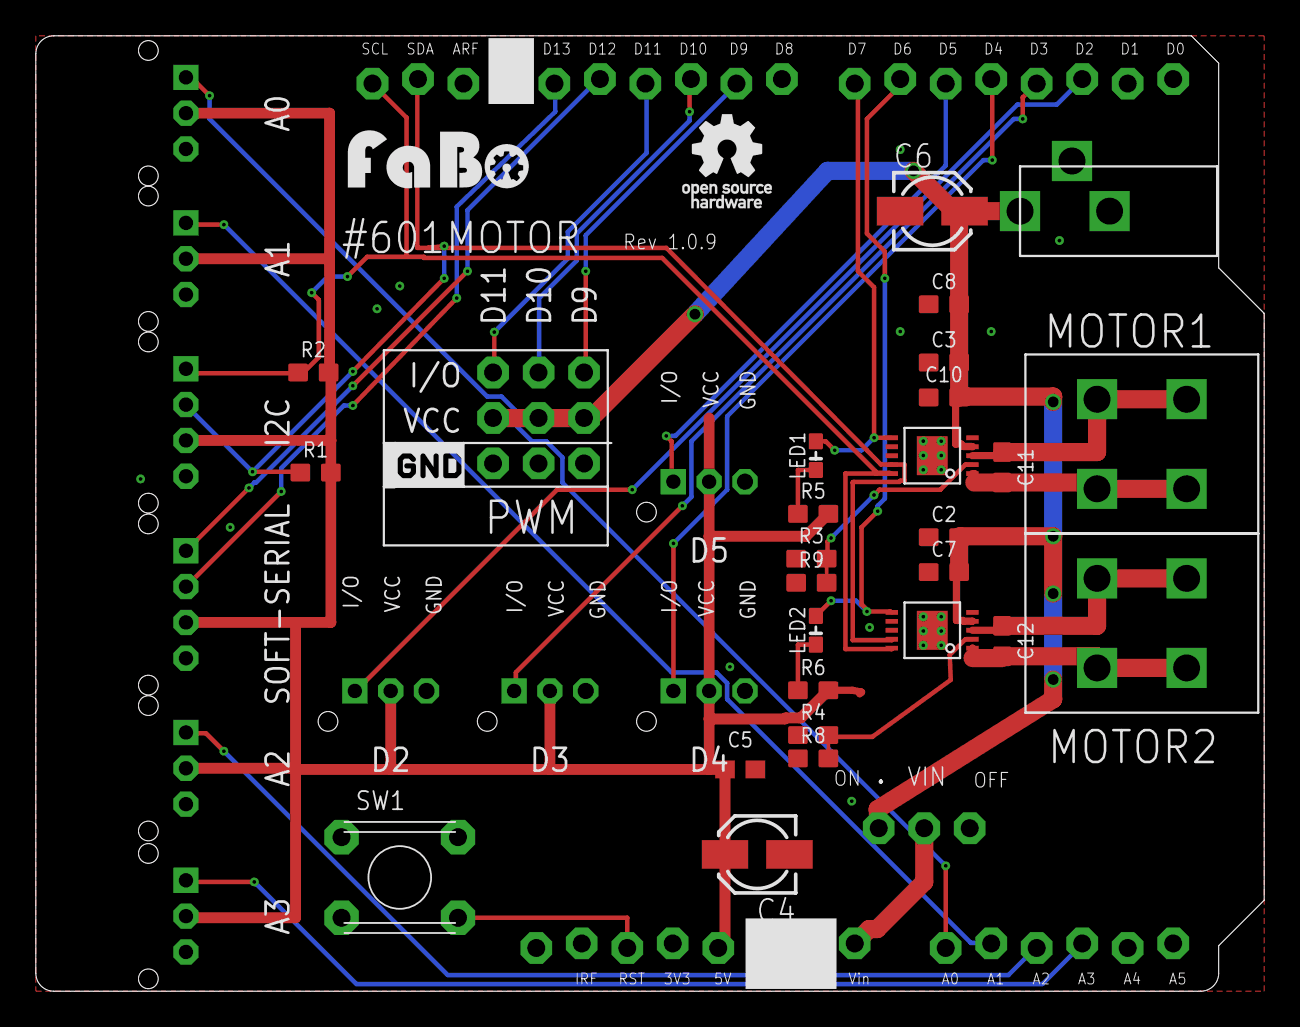
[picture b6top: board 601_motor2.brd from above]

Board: 2 copper layers, 68.6 x 53.3 mm, 44 parts (0 on the bottom side), 30 nets.

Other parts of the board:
U$19: LOGO_SILK_GND

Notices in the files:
parts and their libraries:
FaBo-Template: Released under the Creative Commons Attribution-ShareAlike 4.0 License
https://creativecommons.org/licenses/by-sa/4.0
FaBo-etc: Released under the Creative Commons
